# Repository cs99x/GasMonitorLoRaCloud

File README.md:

# GasMonitorLoRaCloud

The **GasMonitorLoRaCloud** project is a comprehensive IoT solution designed to monitor gas levels using LoRa communication, integrate with cloud platforms for data storage and visualization, and provide mobile app support for real-time monitoring.

## Features

- **Gas Level Monitoring**: Continuously measures gas concentrations using sensors (CH4, CO, LPG, H2).
- **LoRa Communication**: Transmits data over long distances using LoRa technology.
- **Cloud Integration**: Sends collected data to cloud platforms for storage and analysis.
- **Data Visualization**: Offers real-time and historical data visualization through cloud dashboards.
- **iOS Mobile App**: Allows users to scan, connect, and interact with Bluetooth-enabled devices, providing real-time sensor data in a user-friendly interface.

---

## Components

### 1. Hardware

- **Gas Sensor**: Detects specific gas concentrations.
- **LoRa Module**: Manages long-range wireless communication.
- **Microcontroller**: Interfaces with the sensor and LoRa module.
- **Power Supply**: Powers the hardware components.

For detailed information on hardware setup, refer to the respective READMEs:

- [CAD Designs](https://github.com/cs99x/GasMonitorLoRaCloud/blob/main/hardware/cad/README.md)
- [Handheld Gas Meter Firmware](https://github.com/cs99x/GasMonitorLoRaCloud/blob/main/hardware/firmware/handheld-gasmeter/README.md)
- [LoRa-Bluetooth Gateway Firmware](https://github.com/cs99x/GasMonitorLoRaCloud/blob/main/hardware/firmware/lora-bluetooth-gateway/README.md)
- [PCB Design](https://github.com/cs99x/GasMonitorLoRaCloud/blob/main/hardware/pcb-design/README.md)

### 2. Cloud Platform

- **Data Storage**: Collects and stores gas level data received from the LoRa gateway.
- **REST API**: Provides endpoints for receiving sensor data and querying historical records.
- **API Documentation**: Interactive Swagger/OpenAPI documentation for easy API testing and integration.
- **Visualization Tools**: Provides dashboards for monitoring real-time and historical data.
- **Alert Mechanisms**: Notifies users when gas levels exceed predefined thresholds.

For more details on the backend setup, see the [Backend README](https://github.com/cs99x/GasMonitorLoRaCloud/blob/main/backend/README.md).

#### API Endpoints

The backend provides a REST API with the following endpoints:

- **POST `/receive-json`**: Submit sensor data from IoT devices
- **GET `/get-last-entity`**: Retrieve the most recent sensor reading
- **GET `/get-data-from-timestamp`**: Query historical sensor data from a specific timestamp

**Interactive API Documentation**: Access the Swagger UI at `http://<host>:8000/apidocs/` to test the API directly from your browser.

#### API Usage Examples

The Gas Monitor API supports four sensor types: **CH4 (Methane)**, **CO (Carbon Monoxide)**, **LPG (Liquefied Petroleum Gas)**, and **H2 (Hydrogen)**. Below are examples for uploading and retrieving sensor data.

##### Uploading Sensor Data

Use the `POST /receive-json` endpoint to submit sensor readings. Each request can include multiple sensor types in a single payload.

**Example: Uploading CH4 (Methane) Sensor Data**

```bash
curl -X POST http://localhost:8000/receive-json \
  -H "Content-Type: application/json" \
  -d '{
    "pct": 85,
    "id": "sensor-device-1",
    "ts": 1703174400,
    "sensors": [
      {"type": "CH4", "val": 450}
    ]
  }'
```

**Example: Uploading CO (Carbon Monoxide) Sensor Data**

```bash
curl -X POST http://localhost:8000/receive-json \
  -H "Content-Type: application/json" \
  -d '{
    "pct": 90,
    "id": "sensor-device-2",
    "ts": 1703174500,
    "sensors": [
      {"type": "CO", "val": 35}
    ]
  }'
```

**Example: Uploading LPG (Liquefied Petroleum Gas) Sensor Data**

```bash
curl -X POST http://localhost:8000/receive-json \
  -H "Content-Type: application/json" \
  -d '{
    "pct": 78,
    "id": "sensor-device-3",
    "ts": 1703174600,
    "sensors": [
      {"type": "LPG", "val": 120}
    ]
  }'
```

**Example: Uploading H2 (Hydrogen) Sensor Data**

```bash
curl -X POST http://localhost:8000/receive-json \
  -H "Content-Type: application/json" \
  -d '{
    "pct": 92,
    "id": "sensor-device-4",
    "ts": 1703174700,
    "sensors": [
      {"type": "H2", "val": 280}
    ]
  }'
```

**Example: Uploading Multiple Sensor Types Together**

```bash
curl -X POST http://localhost:8000/receive-json \
  -H "Content-Type: application/json" \
  -d '{
    "pct": 88,
    "id": "handheld-meter-1",
    "ts": 1703174800,
    "sensors": [
      {"type": "CH4", "val": 450},
      {"type": "CO", "val": 35},
      {"type": "LPG", "val": 120},
      {"type": "H2", "val": 280}
    ]
  }'
```

**Response Example:**

```json
{
  "received": {
    "pct": 88,
    "id": "handheld-meter-1",
    "ts": 1703174800,
    "sensors": [
      {"type": "CH4", "val": 450},
      {"type": "CO", "val": 35},
      {"type": "LPG", "val": 120},
      {"type": "H2", "val": 280}
    ]
  },
  "system_time": 1703174805
}
```

##### Retrieving Sensor Data

**Get Latest Sensor Reading**

Use `GET /get-last-entity` to retrieve the most recent sensor data entry:

```bash
curl -X GET http://localhost:8000/get-last-entity
```

**Response Example:**

```json
{
  "pct": 88,
  "device_id": "handheld-meter-1",
  "system_time": 1703174805,
  "system_datetime": "2023-12-21T15:20:05",
  "sensors": [
    {"type": "CH4", "val": 450},
    {"type": "CO", "val": 35},
    {"type": "LPG", "val": 120},
    {"type": "H2", "val": 280}
  ]
}
```

**Get Historical Sensor Data**

Use `GET /get-data-from-timestamp` to retrieve sensor data from a specific timestamp onwards:

```bash
curl -X GET "http://localhost:8000/get-data-from-timestamp?system_time=1703174400"
```

**Response Example:**

```json
[
  {
    "pct": 85,
    "device_id": "sensor-device-1",
    "system_time": 1703174405,
    "system_datetime": "2023-12-21T15:13:25",
    "sensors": [
      {"type": "CH4", "val": 450}
    ]
  },
  {
    "pct": 90,
    "device_id": "sensor-device-2",
    "system_time": 1703174505,
    "system_datetime": "2023-12-21T15:15:05",
    "sensors": [
      {"type": "CO", "val": 35}
    ]
  },
  {
    "pct": 78,
    "device_id": "sensor-device-3",
    "system_time": 1703174605,
    "system_datetime": "2023-12-21T15:16:45",
    "sensors": [
      {"type": "LPG", "val": 120}
    ]
  },
  {
    "pct": 92,
    "device_id": "sensor-device-4",
    "system_time": 1703174705,
    "system_datetime": "2023-12-21T15:18:25",
    "sensors": [
      {"type": "H2", "val": 280}
    ]
  }
]
```

### 3. iOS App

The iOS app enhances the project by providing real-time monitoring and interaction with gas sensors via Bluetooth and establishing a connection to the cloud.

#### Key Features

- **Bluetooth Scanning**: Discover nearby Bluetooth Low Energy (BLE) devices.
- **Device Connection**: Connect to selected devices and subscribe to their data notifications.
- **Real-time Sensor Data**: Display detailed information such as battery status, sensor readings, temperature, and alarm statuses.
- **JSON Parsing**: Receive and parse JSON data from devices for structured display.

For detailed setup instructions and usage, refer to the [Mobile README](https://github.com/cs99x/GasMonitorLoRaCloud/blob/main/mobile/README.md).

## Future Enhancements

- Support for additional gas sensors.
- Improved mobile app UI/UX.
- Development of an Android app.
- Advanced cloud-based analytics and reporting.
- Integration with machine learning models for predictive analysis.

---

## License

This project is open-source and licensed under the MIT License. See the [LICENSE](LICENSE) file for details.

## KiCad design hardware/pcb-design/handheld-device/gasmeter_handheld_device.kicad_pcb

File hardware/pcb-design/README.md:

# 2-Layer PCB for ESP32-Based IoT Projects

This project includes a 2-layer PCB design (1.6mm thickness) for an ESP32-based IoT application. The PCB integrates BLE, LoRa, and gas sensors, and is designed to handle power management, sensor interfacing, and user interaction efficiently. This board is intended to be used in upcoming projects with additional hardware and software features.

---

## Key Features

- **ESP32-S3-WROOM-1 Module**: Provides Wi-Fi and BLE capabilities.
- **LoRa Communication Module**: Supports long-range wireless communication.
- **Gas Sensors (MQ Series)**: Interfaces with up to four MQ gas sensors.
- **Power Management**:
  - Integrated **TP4054** Li-ion battery charger.
  - **TPS63020** buck-boost converters for stable power supply.
  - Battery connector and monitoring.
- **User Interaction**:
  - Multiple tactile buttons for input.
  - Integrated WS2812B RGB LEDs for status indication.
- **Peripheral Connections**:
  - USB-C for power and communication.
  - JST connector for Li-ion battery.
- **Compact Design**:
  - 1.6mm thickness, 2-layer PCB.
  - Mounting holes for easy integration into enclosures.

---

## Electrical Specifications

- **Power Input**:
  - USB-C: 5V
  - Li-ion Battery (via JST connector): 3.7V
- **Power Outputs**:
  - 3.3V and 5V rails powered by TPS63020 converters.
- **Current Handling**:
  - 6V 1.2A fuse for overcurrent protection.

---

## PCB Dimensions and Design

- **Layers**: 2
- **Thickness**: 1.6mm
- **Mounting**: Includes 4 mounting holes for M2 screws.
- **Keep-Out Zone**: Clearly marked for sensitive components.

---

## Usage Instructions

1. **Powering the Board**:
   - Connect a USB-C cable for 5V input or use a 3.7V Li-ion battery via the JST connector.
2. **Connecting Sensors**:
   - Plug MQ-series sensors into the designated headers.
3. **Programming**:
   - Use the USB-C port to flash firmware using ESP32 tools.
4. **Testing**:
   - Observe RGB LEDs and Serial Monitor for system status and debug messages.

---

## License

This project is licensed under the MIT License.

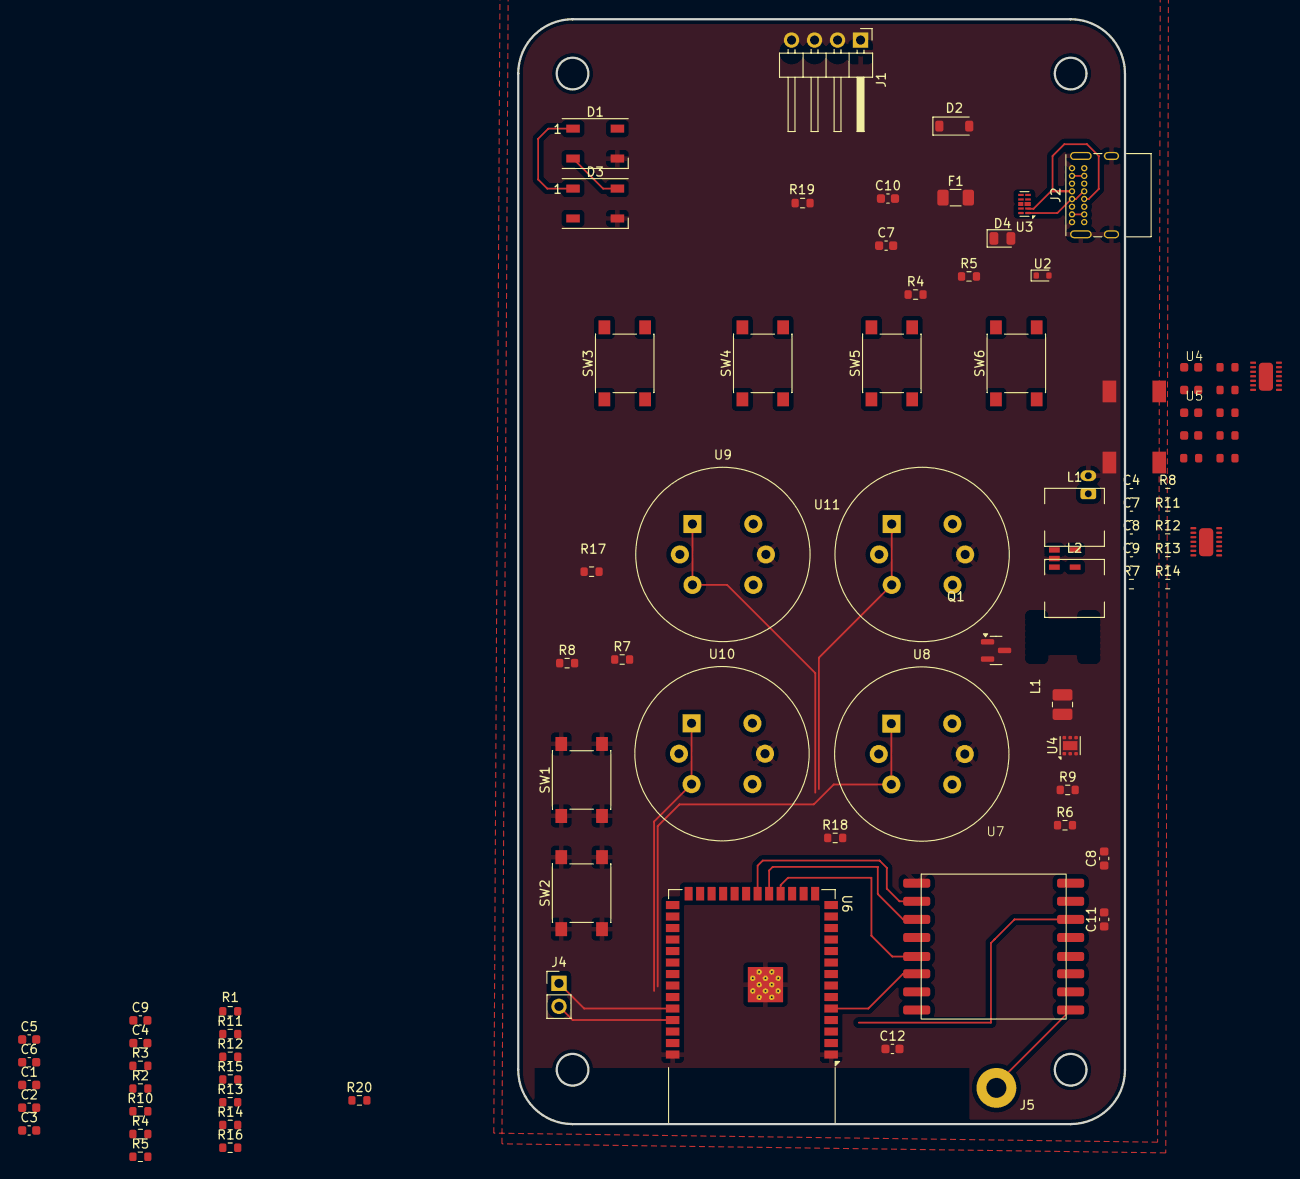
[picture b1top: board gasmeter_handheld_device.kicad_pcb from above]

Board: 2 copper layers, 67.0 x 122.0 mm, 76 parts (1 on the bottom side), 47 nets.

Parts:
C1, C4, C7, C7#2, C8#2, C12: 10uF/6.3v; C_0603_1608Metric
C2: 220nF/6.3v; C_0603_1608Metric
C3: 1uF/6.3v; C_0603_1608Metric
C4#2, C9#2: 100nF/6.3v; C_0603_1608Metric
C5, C6, C10: 0.1uF; C_0603_1608Metric
C8: 2.2uF/6.3v; C_0603_1608Metric
C9: 220uF/6.3v; C_0603_1608Metric
C11: 10uF; C_0603_1608Metric
D1, D3: WS2812B; LED_WS2812B_PLCC4_5.0x5.0mm_P3.2mm
D2: 1N5819; D_SOD-123
D4: LED; LED_0805_2012Metric
F1: 6V 1.2A; Fuse_1206_3216Metric
J1: Conn_01x04_Pin; PinHeader_1x04_P2.54mm_Horizontal
J2: USB_C_Receptacle_USB2.0_16P; USB_C_Receptacle_GCT_USB4085
J3: JST PH-1.25-2P LiPo connector; JST_PH_B2B-PH-K_1x02_P2.00mm_Vertical
J4: Conn_01x02_Pin; PinHeader_1x02_P2.54mm_Vertical
J5: Conn_Coaxial; MountingHole_2.2mm_M2_Pad
L1: 6.8uH; L_1008_2520Metric
L1#2, L2: 1.5uH; L_6.3x6.3_H3
Q1: AO3401A; SOT-23
R1: 2K; R_0603_1608Metric
R2, R3: 5.1k; R_0603_1608Metric
R4, R5#2, R6, R9, R10: 10k; R_0603_1608Metric
R4#2: 10K; R_0603_1608Metric
R5: 1K; R_0603_1608Metric
R7, R8#2, R11, R14: 1M; R_0603_1608Metric
R7#2: 2.5M; R_0603_1608Metric
R8: 500K; R_0603_1608Metric
R11#2, R12: 180k; R_0603_1608Metric
R12#2, R14#2, R16: 200K; R_0603_1608Metric
R13: 1.8M; R_0603_1608Metric
R13#2: 1.6M; R_0603_1608Metric
R15, R17, R18, R19, R20: 5.1K; R_0603_1608Metric
SW1: BOOT; SW_Push_1P1T_NO_6x6mm_H9.5mm
SW2: RESET; SW_Push_1P1T_NO_6x6mm_H9.5mm
SW3, SW4, SW5, SW6: SW_MEC_5E; SW_Push_1P1T_NO_6x6mm_H9.5mm
U1: TP4054; SOT23-5L
U2: RSB6.8S; D_SOD-523
U3: ESD7104MUTAG; Diodes_UDFN-10_1.0x2.5mm_P0.5mm
U4, U5: TPS63020
U4#2: TLV75801PDRV; WSON-6-1EP_2x2mm_P0.65mm_EP1x1.6mm
U6: ESP32-S3-WROOM-1
U7: LoRa 16x16 Modul; 16x16 LoRa
U8, U9, U10, U11: MQ-4; MQ-6

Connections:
/3V3: C7.1, C10.1, C11.1, C12.1, J1.2, R4.2, R5#2.2, R6.1, R7.2, R8#2.1, R9.1, R10.2, R11.2, R15.2, U4.4 (VOUT), U4#2.1 (OUT), U6.2 (3V3), U7.12 (3.3V)
/5V: C1.1, C8.1, C9.1, D1.1 (VDD), D3.1 (VDD), R13.2, R13#2.1, R14.2, R16.2, U1.4 (VCC), U5.4 (VOUT), U8.2 (VH+), U8.4 (A2), U8.6 (A1), U9.2 (VH+), U9.4 (A2), U9.6 (A1), U10.2 (VH+), U10.4 (A2), U10.6 (A1), U11.2 (VH+), U11.4 (A2), U11.6 (A1)
/5VUSB: F1.1, J2.A4 (VBUS), J2.A9 (VBUS), J2.B4 (VBUS), J2.B9 (VBUS), U3.4, U3.7 (NC)
/CHRG: U1.1 (CHRG), U6.32 (IO39)
/DIO0: U6.6 (IO6), U7.11 (DIO0)
/ESP32_EN: C5.1, R10.1, U6.3 (EN)
/I2C_SCL_OLED: J1.3, R4.1, R9.2, U6.17 (IO9)
/I2C_SDA_OLED: J1.4, R5#2.1, R6.2, U6.12 (IO8)
/LED_Data: D1.4 (DIN), U6.7 (IO7)
/MISO: U6.20 (IO12), U7.2 (MISO)
/MOSI: U6.19 (IO11), U7.3 (MOSI)
/MQ4ANALOG: R17.1, U6.39 (IO1), U8.1 (B1), U8.3 (B2)
/MQ6ANALOG: R19.1, U6.38 (IO2), U10.1 (B1), U10.3 (B2)
/MQ7ANALOG: R18.1, U6.15 (IO3), U9.1 (B1), U9.3 (B2)
/MQ8ANALOG: R20.1, U6.4 (IO4), U11.1 (B1), U11.3 (B2)
/NSS: U6.18 (IO10), U7.5 (NSS)
/RESET: U6.5 (IO5), U7.6 (RESET)
/RXD: J4.1, U6.36 (RXD0)
/SCK: U6.22 (IO14), U7.4 (SCK)
/SW1: SW3.1, SW3.2, U6.28 (IO35)
/SW2: SW4.1, SW4.2, U6.29 (IO36)
/SW3: SW5.1, SW5.2, U6.30 (IO37)
/SW4: SW6.1, SW6.2, U6.31 (IO38)
/TXD: J4.2, U6.37 (TXD0)
/USB_N: J2.A7 (D-), J2.B7 (D-), U3.2, U3.9 (NC), U6.14 (IO20)
/USB_P: J2.A6 (D+), J2.B6 (D+), U3.1, U3.10 (NC), U6.13 (IO19)
/VBAT: C2.1, J3.1, Q1.3 (D), U1.3 (BAT)
GND: C1.2, C2.2, C3.2, C4.2, C4#2.2, C5.2, C6.2, C7.2, C8.2, C9.2, C9#2.2, C10.2, C11.2, C12.2, D1.3 (VSS), D3.3 (VSS), D4.1 (K), J1.1, J2.A1 (GND), J2.A12 (GND), J2.B1 (GND), J2.B12 (GND), J2.S1 (SHIELD), J3.2, R1.1, R2.2, R3.2, R4#2.1, R7.1, R8.1, R11#2.2, R12.2, R12#2.1, R14.1, R14#2.1, R16.1, R17.2, R18.2, R19.2, R20.2, SW1.1, SW1.2, SW2.1, SW2.2, U1.2 (GND), U2.2 (D), U3.3 (VSS), U3.8 (VSS), U4.2 (GND), U4.14 (PG), U4#2.3 (GND), U4#2.7 (GND), U5.2 (PGND), U5.14 (PG), U6.1 (GND), U6.40 (GND), U6.41 (GND), U7.1 (GND), U7.8 (GND), U7.15 (GND), U8.5 (VH-), U9.5 (VH-), U10.5 (VH-), U11.5 (VH-)
unnamed: D1.2 (DOUT), D3.4 (DIN)
unnamed: D2.2 (A), F1.2, R4#2.2, R5.2, U2.1 (D)
unnamed: C3.1, C4.1, C7#2.1, C8#2.1, D2.1 (K), L1.1, Q1.2 (S), R7#2.2, U4.10 (VIN), U4#2.4 (EN), U4#2.6 (IN), U5.10 (VIN)
unnamed: D4.2 (A), R15.1
unnamed: J2.A5 (CC1), R2.1
unnamed: J2.B5 (CC2), R3.1
unnamed: J5.1 (In), U7.16 (ANT)
unnamed: Q1.1 (G), R5.1
unnamed: C6.1, U6.27 (IO0)
unnamed: R1.2, U1.5 (PROG)
unnamed: C4#2.1, C7#2.2, U4.1 (VINA), U4.12 (EN), U4.13 (PS/SYNC)
unnamed: R8#2.2, R11.1, R11#2.1, R12#2.2, U4.3 (FB), U4#2.2 (FB)
unnamed: L1#2.1, U4.8 (L1)
unnamed: L1#2.2, U4.6 (L2)
unnamed: C8#2.2, C9#2.1, U5.1 (VINA), U5.12 (EN), U5.13 (PS/SYNC)
unnamed: R12.1, R13.1, R13#2.2, R14#2.2, U5.3 (FB)
unnamed: L2.1, U5.8 (L1)
unnamed: L2.2, U5.6 (L2)
unnamed: R7#2.1, R8.2

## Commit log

2024-10-20 Added folder structure
2024-10-25 new folder structure
2024-10-25 Update folder structure
2024-10-27 first rn app
2024-11-11 HelloWorld Handheld Device
2024-11-12 hello world backend
2024-12-20 Fix Local Repo issue
2024-12-27 Fix repo
2024-12-27 App mit neuen Gasen
2024-12-27 set up backend
2024-12-27 test
2024-12-27 Flask backend
2024-12-27 backend
2024-12-27 Neu geordnet
2024-12-27 neu geordnet 2
2024-12-27 ordnung letze
2024-12-27 test commit
2024-12-27 test123
2024-12-30 mock data
2024-12-30 running flask server
2025-01-01 Add KiCad project to specific folder
2025-01-01 Add .gitignore for KiCad project
2025-01-02 Timestamp, Battery etc.. in App eingebaut
2025-01-03 handheld gasmeter firmware
2025-01-03 Create GasSensorReadingv2(temporary)
    Readout of 4 Gassensors
2025-01-03 Rename GasSensorReadingv2(temporary) to GasSensorReadingv2(temporary).ino
    addesd ".ino" to file name
2025-01-03 UPLOAD OF IMPROVED VERSION OF THE gAS
2025-01-03 Update GasSensorReadingV3.ino
    small changes in the waring of the JSON
2025-01-04 Working handheld gasmeter and lora gateway
2025-01-04 Backend running
2025-01-05 conversion from Voltage to PPM ,Added Screenfunctionality with Button
    Screen0: overview over all 4 Sensors
    Screen 1-4: gases of its own
    screen 5: Battery and alert threshold for all gases
    screen 6 : LoRa Connection status
2025-01-06 First Mutitask test
    LED1 on.......off.......on....off.......on......off
    LED2 on..off..on...off....on...off...on...off
2025-01-06 Mutitask part for Handhelddevice, LoRa part missing
    merger of firstMultiTaskLEDblink.ino and GasSensorReadingV3.ino
2025-01-06 first buzzer implementaition
    First test for buzzer
    reworked comments
    time to go to bed
2025-01-06 fixed structure
2025-01-06 rename
2025-01-06 Handheld multitaaskin without lora
2025-01-06 Create handheldSensorAndLoRa
    A File to merge The Sensor File and The LoRa implementaion
2025-01-06 Merging
2025-01-06 neue struktur, neue main page, second page added with historical data
2025-01-07 Refactoring/ Modularization
2025-01-07 fixed second page database
2025-01-08 changed o2 to lpg
2025-01-08 updated dependencies
2025-01-08 Frontend + Backend extension
2025-01-08 LoRa + Display +Sensors working
    Blocking code, Reading out Sensors and putting them in a JSON. JSON gets transmitted via LoRa. The Sensor Values Are shown on a display
2025-01-15 added display functionality with button
2025-01-21 Optimize code, creating readme, code cleanup
2025-01-21 Clean project structure add readme
2025-01-21 Optimize project structure + cleanup
2025-01-21 Cleanup
2025-01-21 readme
2025-01-21 cleanup + readme
2025-01-22 Create LICENSE
2025-01-22 Update LICENSE
2025-01-22 KiCad files modified
2025-01-22 Add comments
2025-01-22 Optimize website + gitiginore
2025-01-22 Untracked files listed in .gitignore
2025-01-26 Add files via upload
    PCB rendering
2025-12-18 Initial plan
2025-12-18 Add Swagger/OpenAPI documentation to Flask API
2025-12-18 Fix Swagger docstrings and improve database path configuration
2025-12-18 Fix Swagger UI URL paths in documentation
2025-12-18 Revert database path changes, keep only Swagger documentation
2025-12-21 Add comprehensive sensor API examples to main README
2025-12-21 Fix typo: conectiontion -> connection
